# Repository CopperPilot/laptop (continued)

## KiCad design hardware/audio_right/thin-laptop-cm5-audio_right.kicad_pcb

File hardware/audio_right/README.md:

# Right Audio & Microphone Sub-Board (`audio_right`)

## Overview
- **Project**: `hardware/audio_right/thin-laptop-cm5-audio_right.kicad_pro`
- **Dimensions**: `36.0 mm x 38.0 mm`, 2-layer FR-4 PCB (`1.6 mm` thickness, `2.0 mm` corner radius)
- **World Placement**: `[190.5, -4.0, 0.0] mm` inside the 13-inch thin aluminum laptop lower deck
- **Mating Cable (`c_audio_right`)**: 8-pin `0.5 mm` pitch **Type-B (opposite-side / reversed-contact)** FFC ribbon (`45.0 mm` length) connecting main-board bottom-contact `J_AUDR` (`FPC-05F-8PH20`, LCSC `C2856797`, contacts `-Z`, Pad 1 at South `y=23.75 mm`, Pad 8 at North `y=20.25 mm`) 1-to-1 to `audio_right` top-contact `J2` (`FPC-05FB-8PH20`, LCSC `C2856828`, contacts `+Z`, Pad 1 at South `y=19.75 mm`, Pad 8 at North `y=16.25 mm`)

---

## Sub-Board Architecture & Design Review Verification

1. **CTIA / AHJ 3.5 mm 6-Pin Switched TRRS Jack Mapping (`J1`, XKB Connection `PJ-3701-SMT`, LCSC `C2684645`, `[P1]` Resolved)**:
   - Replaced unswitched 4-pin `PJ-320D` with 6-pin `XKB Connection PJ-3701-SMT` (LCSC `C2684645`, `lcsc:AUDIO-SMD_PJ-3701-SMT`) placed at `(28.50, 19.00) mm`, `rot = 180.0 deg` on `F.Cu` (`mouth` facing `+X` `[1, 0, 0]` into right-edge case cutout `F_AUDIO`).
   - Verified pin-to-contact mapping against the `PJ-3701-SMT` mechanical drawing and schematic (`SCHEMATIC(PLUG OUT)`):
     - **Pin 4 (Tip, `12.21 mm` deepest contact at pad `(24.02, 22.85) mm`)**: `/HP_L_JACK` (Left headphone audio).
     - **Pin 3 (Ring 1, `4.79 mm` middle contact at pad `(30.02, 22.85) mm`)**: `/HP_R_JACK` (Right headphone audio).
     - **Pin 2 (Ring 2, `7.84 mm` common return contact at pad `(32.98, 15.15) mm`)**: `/GND` (CTIA common ground return, Kelvin-sensed via `C20 = 2.2 uF` placed at `(32.30, 12.50) mm` with dedicated `F.Cu` Kelvin trace directly to `J1.2` and `R29 = 1.3 kOhm` into `/HS_REF_MUX`).
     - **Pin 1 (Sleeve, `1.81 mm` entrance contact at pad `(31.92, 22.85) mm`)**: `/HS_MIC_DET` (CTIA headset microphone & bias/sense, clamped by unidirectional 3.3 V ESD diode `D3` `PESD3V3U1UA,115`, LCSC `C403915`).
     - **Pin 5 (`/TIP_SW` at pad `(24.02, 15.15) mm`) & Pin 6 (`/GND` at pad `(26.02, 15.15) mm`)**: Isolated Normally-Closed (NC) Mechanical Tip Plug-Detect Switch (`5 VDC`, `0.5 A`, `<= 70 mOhm` closed resistance). When unplugged (`PLUG OUT`), Pin 5 is shorted to Pin 6 (`/GND`), holding `/TIP_SW = 0.000 V`. When any 3.5 mm plug is fully seated, Tip lifts insulator block `#9` to open Pin 5 from Pin 6, allowing `/TIP_SW` to charge via `R30 = 22 kOhm` (`C25768`) toward `/+2V8_ANA` (`2.80 V`) across `C23 = 2.2 uF` (`C159814`, `tau = 48.4 ms`, crossing `U1` rising threshold `V_TH+ = 2.365 V` at `t_qual = 90.1 ms` after contact bounce and Sleeve insertion wiping have completed), protected by ESD diode `D10` (`PESD3V3U1UA,115`, LCSC `C403915`).

2. **Decoupled Mechanical Headphone Plug Detection (`U1`) & Deterministic Monostable Microphone Source Selection (`U2, U3`, `3x TI TLV7041DBVR`, LCSC `C702122`, `[P1]` & `[P2]` Resolved)**:
   - **Headphone Plug Detection (`U1` driving `/HP_DET_N -> R4 = 1 kOhm -> /HP_DET` on `J2.7`)**:
     - `U1.4` (`IN-`) senses `/TIP_SW`; `U1.3` (`IN+`) senses `/U1_INP` (`V_REF_HI = 2.344 V` via `R23 = 22 kOhm` with `R31 = 1 MOhm` positive feedback to `/HP_DET_N`, giving `V_TH+ = 2.365 V` rising at `t = 90.1 ms` and `V_TH- = 2.293 V` falling, `72 mV` hysteresis).
     - `/HP_DET` is **100% independent of Sleeve microphone impedance**: inline hardware mic-mute switches (`R_sleeve = inf`), detached boom mics, or open-mic Y-splitters never cause false unplug events on `/HP_DET`.
   - **Synchronous Debounced Plug-Presence Gate (`U2`) & Deterministic 3-Pole TRS vs 4-Pole CTIA Classifier (`U3`) on `/MIC_SEL` (`R17 = 2.2 kOhm` pull-up to `/+3V3`)**:
     - Reference divider on `/+2V8_ANA` (`2.80 V`): `R13 = 2.2 kOhm`, `R14 = 10 kOhm`, `R16 = 1.3 kOhm` (`C25866`) -> `V_REF_HI = 2.344 V` (`C17 = 100 nF`), `V_REF_LO = 0.270 V` (`C18 = 100 nF`).
     - **Synchronous Plug-Presence Gate (`U2`)**: `U2.3` (`IN+`) = `/V_REF_HI` (`2.344 V`), `U2.4` (`IN-`) = `/HP_DET_N` (driven directly by `U1.1`'s debounced output with `72 mV` hysteresis). Whenever unplugged (`V_TIP_SW < 2.365 V`) or during the first `90.1 ms` of plug insertion (`/HP_DET_N = 3.30 V`), `U2.1` holds `/MIC_SEL` LOW (`0.00 V`, selecting internal MEMS mic `MK1`). Once `U1` qualifies the seated plug at `t = 90.1 ms` (`/HP_DET_N = 0.00 V`), `U2.1` releases `/MIC_SEL` synchronously with `/HP_DET_N`.
     - **Non-Loading Sleeve Sense Tap & Rail-to-Rail Clamp (`R12, C12, D11`)**:
       - Sleeve `/HS_MIC_DET` is sensed through high-impedance `R12 = 47 kOhm` (`C25792`) and `C12 = 4.7 nF` (`C1538`, `tau = 221 us << 90.1 ms`), loading the positive mic leg by `< 0.2 dB` across `20 Hz .. 20 kHz` so `/HS_MIC_MUX` (`1.29 kOhm .. 1.32 kOhm`) stays balanced within `1.5%` of `/HS_REF_MUX` (`R29 = 1.30 kOhm`).
       - `D11` (`BAV99,215`, LCSC `C2500`, `I_R < 1 nA` typ) clamps `/DET_IN` between `/GND` (Pin 1) and `/+2V8_ANA` (Pin 2) behind `R12 = 47 kOhm`, ensuring `/DET_IN` never exceeds `-0.3 V` or `+2V8_ANA + 0.3 V`.
     - **Deterministic 3-Pole TRS vs 4-Pole CTIA Selection (`U3`)**:
       - `U3.4` (`IN-`) = `/V_REF_LO` (`0.270 V`); `U3.3` (`IN+` = `/U3_INP`) is connected via `R27 = 2.2 kOhm` (`C25879`) to `/DET_IN` with `R28 = 1 MOhm` (`C26083`) hysteresis to `/MIC_SEL`.
       - **3-Pole TRS Headphones (`R_sleeve < 100 Ohm`, e.g. `0 Ohm` grounded Sleeve)**: `V_HS_MIC_DET < 0.100 V` settles on `/DET_IN` in `< 1.1 ms << 90.1 ms`. Even if `/MIC_SEL` were transiently `3.30 V`, `V_U3P(R_sleeve = 0 Ohm, MIC_SEL = 3.30 V) = 3.30 V * (47k + 2.2k) / (47k + 2.2k + 1000k) = 0.155 V < V_REF_LO (0.270 V)` (`V_TH- = 0.121 V` [`120 Ohm`], `V_TH+ = 0.283 V` [`300 Ohm`]). Thus `U3.1` deterministically holds or resets `/MIC_SEL = 0.00 V` (internal mic `MK1`) with **zero bistable lockup** on TRS contact bounce.
       - **4-Pole CTIA Headset (`680 Ohm <= R_sleeve <= 10 kOhm`, or `R_sleeve = inf` when inline hardware mute switch is open at boot, plug-in, or during capture)**: `0.568 V <= V_HS_MIC_DET <= 2.800 V -> 0.541 V <= V_U3P <= 2.823 V > V_REF_LO (0.270 V)`. Both `U2.1` and `U3.1` release `/MIC_SEL` to `3.30 V`, switching `U4` (`TS5A23159DGSR`) to the external headset microphone (`NO1/NO2`) so a muted CTIA headset never silently falls back to internal mic `MK1`.

3. **Ultra-Low-Noise 2.8 V Analog LDO & Back-Drive Protection (`U5`, TI `LP5907MFX-2.8/NOPB`, LCSC `C186700`, `R24`, `D12`, `[P1]` Resolved)**:
   - Powered from `/+3V3` with local `1 uF` input cap `C22` (`C52923`) within `1.5 mm` of `U5.1`/`U5.2` and local `1 uF` output cap `C21` (`C52923`) on `/+2V8_ANA`.
   - `R24 = 1.3 kOhm` (`C25866`) minimum preload bleeder from `/+2V8_ANA` to `/GND` (`2.154 mA`) combines with the reference dividers (`0.237 mA`) and `MK1` (`0.185 mA` min) to guarantee `>= 2.575 mA` continuous sink load on `/+2V8_ANA`, exceeding the maximum back-drive current (`(6.0 V - 2.8 V) / (2.67k || 47k) = 1.27 mA`) under external `3 V .. 6 V` faults on `J1.1` before `D3` (`PESD3V3U1UA,115`) and `D12` (`PESD3V3U1UA,115` on `/+2V8_ANA`) clamp to `/GND`.

4. **Dual SPDT Differential Microphone Multiplexer (`U4`, TI `TS5A23159DGSR`, LCSC `C42751`) & Matched Low-Leakage Silicon Clamps (`D8, D9`, `BAV99,215`, LCSC `C2500`)**:
   - Biased at `/MUX_BIAS_FILT = 0.795 V` via `R18 = 68 kOhm` (`C36871`) and `R19 = 27 kOhm` (`C25771`) from `/+2V8_ANA`, matching `MK1` (`ICS-40720`) `0.80 V` DC common-mode output within `5 mV` for clickless switching.
   - Clamped by matched ultra-low-leakage dual-series silicon diodes `D8` (on `/HS_MIC_MUX`) and `D9` (on `/HS_REF_MUX`) between `/GND` and `/+3V3`.

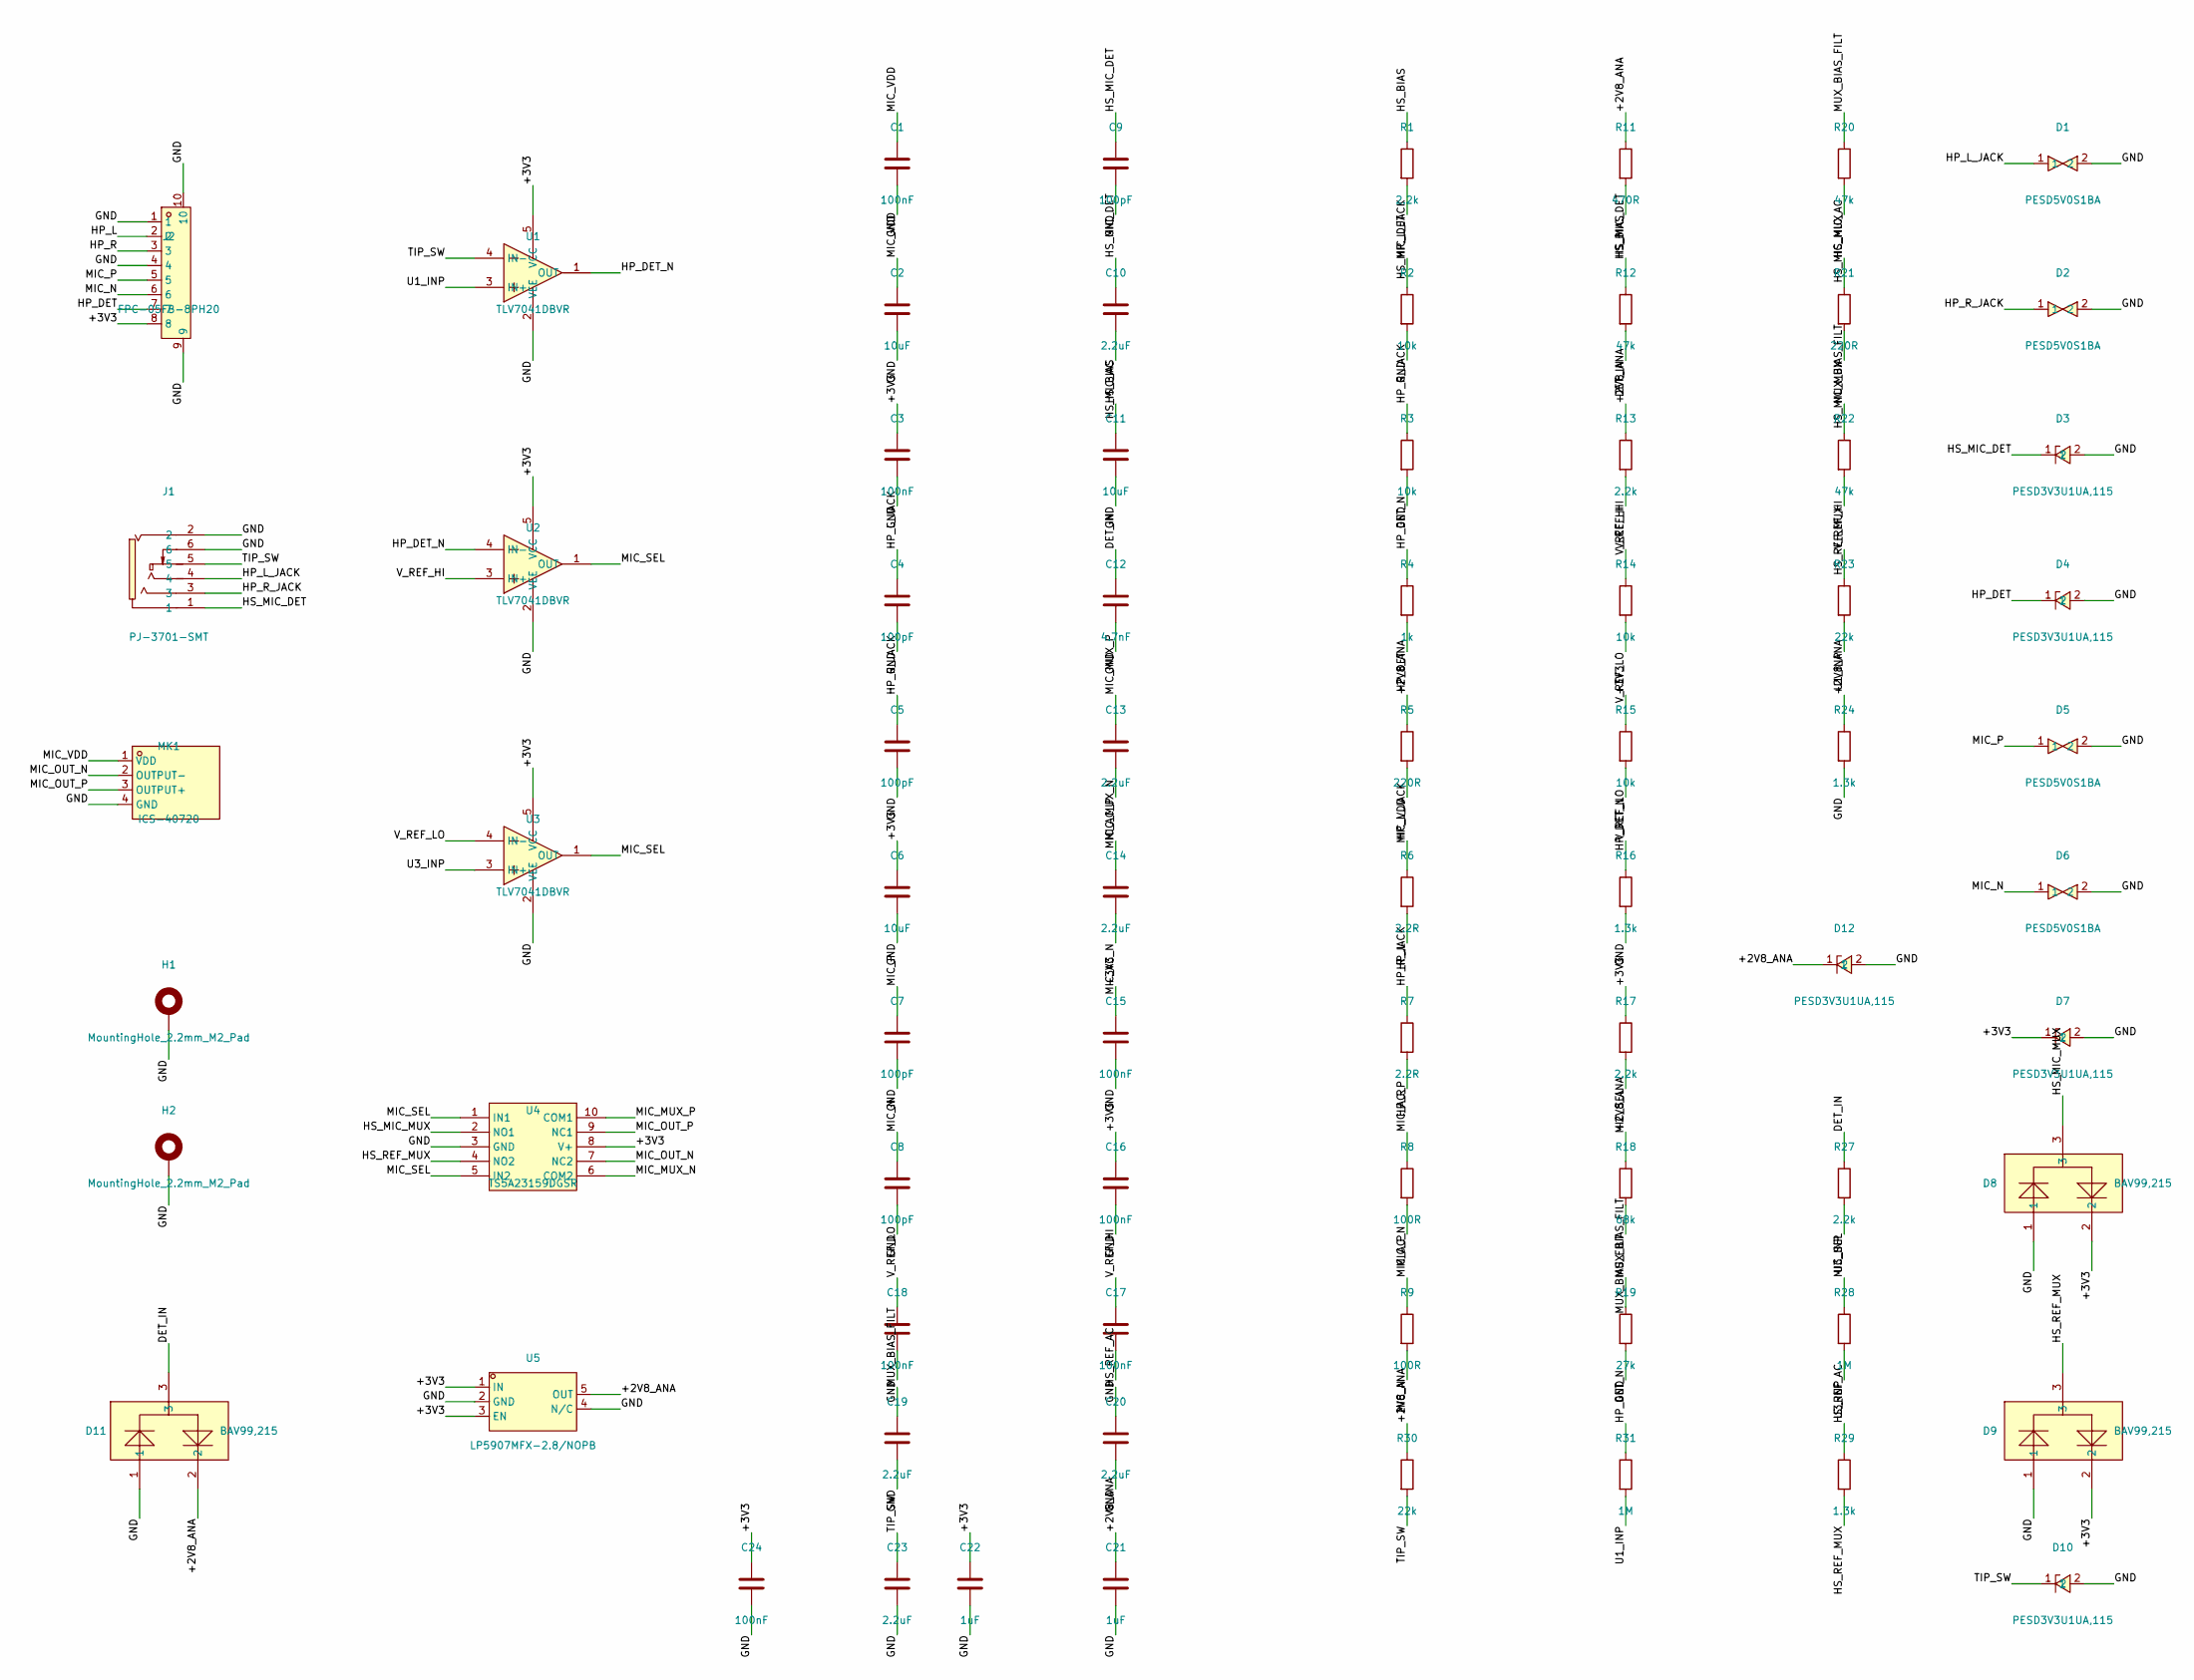
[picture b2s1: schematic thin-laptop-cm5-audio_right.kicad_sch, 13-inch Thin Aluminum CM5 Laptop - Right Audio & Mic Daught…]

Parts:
C1, C3, C15, C16, C17, C18, C24: 100nF; C_0402_1005Metric; LCSC C85858
C2, C6, C11: 10uF; C_0603_1608Metric; LCSC C96446
C4, C5, C7, C8, C9: 100pF; C_0402_1005Metric; LCSC C1546
C10, C13, C14, C19, C20, C23: 2.2uF; C_0402_1005Metric; LCSC C159814
C12: 4.7nF; C_0402_1005Metric; LCSC C1538
C21, C22: 1uF; C_0402_1005Metric; LCSC C52923
D1, D2, D5, D6: PESD5V0S1BA; SOD-323_L1.7-W1.3-LS2.5-BI; LCSC C2827694
D3, D4, D7, D10, D12: PESD3V3U1UA,115; SOD-323_L1.7-W1.3-LS2.5-RD; LCSC C403915
D8, D9, D11: BAV99,215; SOT-23-3_L2.9-W1.6-P1.90-LS2.8-BR; LCSC C2500
H1, H2: MountingHole_2.2mm_M2_Pad
J1: PJ-3701-SMT; AUDIO-SMD_PJ-3701-SMT; LCSC C2684645
J2: FPC-05FB-8PH20; FPC-SMD_8P-P0.50_XUNPU_FPC-05FB-8PH20; LCSC C2856828
MK1: ICS-40720; SMD_4P-P0.88_ICS-40720; LCSC C3171779
R1, R13, R17, R27: 2.2k; R_0402_1005Metric; LCSC C25879
R2, R3, R14, R15: 10k; R_0402_1005Metric; LCSC C25744
R4: 1k; R_0402_1005Metric; LCSC C11702
R5, R21: 220R; R_0402_1005Metric; LCSC C25091
R6, R7: 2.2R; R_0402_1005Metric; LCSC C25101
R8, R9: 100R; R_0402_1005Metric; LCSC C25076
R11: 470R; R_0402_1005Metric; LCSC C25117
R12, R20, R22: 47k; R_0402_1005Metric; LCSC C25792
R16, R24, R29: 1.3k; R_0402_1005Metric; LCSC C25866
R18: 68k; R_0402_1005Metric; LCSC C36871
R19: 27k; R_0402_1005Metric; LCSC C25771
R23, R30: 22k; R_0402_1005Metric; LCSC C25768
R28, R31: 1M; R_0402_1005Metric; LCSC C26083
U1, U2, U3: TLV7041DBVR; SOT-23-5_L2.9-W1.6-P0.95-LS2.8-BR; LCSC C702122
U4: TS5A23159DGSR; VSSOP-10_L3.0-W3.0-P0.50-LS4.9-BL; LCSC C42751
U5: LP5907MFX-2.8/NOPB; TSOT-23-5_L2.9-W1.6-P0.95-LS2.8-BL; LCSC C186700

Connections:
/+2V8_ANA: C21.1, D11.2, D12.1, R5.1, R11.1, R13.1, R18.1, R24.1, R30.1, U5.5 (OUT)
/+3V3: C3.1, C6.1, C15.1, C16.1, C22.1, C24.1, D7.1, D8.2, D9.2, J2.8, R15.1, R17.1, U1.5 (VCC), U2.5 (VCC), U3.5 (VCC), U4.8 (V+), U5.1 (IN), U5.3 (EN)
/DET_IN: C12.1, D11.3, R12.2, R27.1
/GND: C1.2, C2.2, C3.2, C4.2, C5.2, C6.2, C7.2, C8.2, C9.2, C11.2, C12.2, C15.2, C16.2, C17.2, C18.2, C19.2, C20.2, C21.2, C22.2, C23.2, C24.2, D1.2, D2.2, D3.2, D4.2, D5.2, D6.2, D7.2, D8.1, D9.1, D10.2, D11.1, D12.2, H1.1, H2.1, J1.2, J1.6, J2.1, J2.4, J2.9, J2.10, MK1.4 (GND), R2.2, R3.2, R16.2, R19.2, R24.2, U1.2 (VEE), U2.2 (VEE), U3.2 (VEE), U4.3 (GND), U5.2 (GND), U5.4 (N/C)
/HP_DET: D4.1, J2.7, R4.2
/HP_DET_N: R4.1, R15.2, R31.1, U1.1 (OUT), U2.4 (IN-)
/HP_L: J2.2, R6.2
/HP_L_JACK: C4.1, D1.1, J1.4, R2.1, R6.1
/HP_R: J2.3, R7.2
/HP_R_JACK: C5.1, D2.1, J1.3, R3.1, R7.1
/HS_BIAS: C11.1, R1.1, R11.2
/HS_MIC_AC: C10.2, R21.1
/HS_MIC_DET: C9.1, C10.1, D3.1, J1.1, R1.2, R12.1
/HS_MIC_MUX: D8.3, R20.2, R21.2, U4.2 (NO1)
/HS_REF_AC: C20.1, R29.1
/HS_REF_MUX: D9.3, R22.2, R29.2, U4.4 (NO2)
/MIC_AC_N: C14.2, R9.1
/MIC_AC_P: C13.2, R8.1
/MIC_MUX_N: C14.1, U4.6 (COM2)
/MIC_MUX_P: C13.1, U4.10 (COM1)
/MIC_N: C8.1, D6.1, J2.6, R9.2
/MIC_OUT_N: MK1.2 (OUTPUT−), U4.7 (NC2)
/MIC_OUT_P: MK1.3 (OUTPUT+), U4.9 (NC1)
/MIC_P: C7.1, D5.1, J2.5, R8.2
/MIC_SEL: R17.2, R28.1, U2.1 (OUT), U3.1 (OUT), U4.1 (IN1), U4.5 (IN2)
/MIC_VDD: C1.1, C2.1, MK1.1 (VDD), R5.2
/MUX_BIAS_FILT: C19.1, R18.2, R19.1, R20.1, R22.1
/TIP_SW: C23.1, D10.1, J1.5, R30.2, U1.4 (IN-)
/U1_INP: R23.2, R31.2, U1.3 (IN+)
/U3_INP: R27.2, R28.2, U3.3 (IN+)
/V_REF_HI: C17.1, R13.2, R14.1, R23.1, U2.3 (IN+)
/V_REF_LO: C18.1, R14.2, R16.1, U3.4 (IN-)

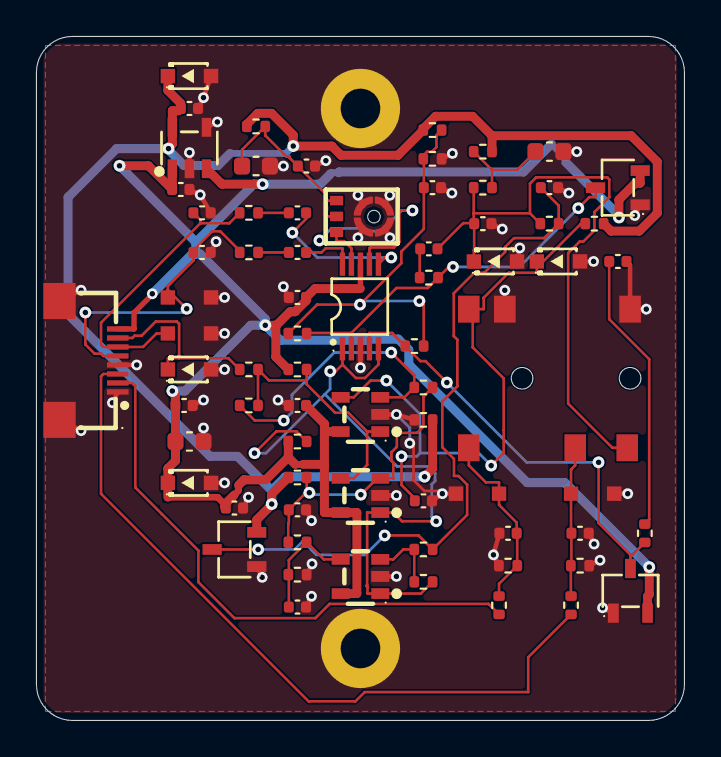
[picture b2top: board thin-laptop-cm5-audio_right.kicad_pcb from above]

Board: 2 copper layers, 36.0 x 38.0 mm, 74 parts (0 on the bottom side), 32 nets.

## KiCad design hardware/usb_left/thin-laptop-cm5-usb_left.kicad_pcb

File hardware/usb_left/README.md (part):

# Left Dual USB-C PD & Data Daughter Board (`usb_left`)

## 1. Architecture & Block Summary (`usb_left_subboard`)

`usb_left` is a **4-layer 1.6 mm controlled-impedance FR-4 PCB** (matching the main board stackup with `0.1068 mm` outer prepreg over continuous `In1.Cu`, `In2.Cu`, and `B.Cu` `GND` reference planes). All components on `usb_left` are assembled on the top side (`F.Cu` only, `0` bottom-side components) so the CNC aluminum `bottom_shell` underneath `usb_left` is a continuous unperforated pan with no through-cutouts.

### 1.1 Front-Left 20 V (45 W Hardware-Capped from 45–65 W Adapters, with 5 V–20 V Autonomous Dead-Battery VINDPM Startup) USB-C PD 3.0 Charging & Host Data Port (`J2`, `TYPE-C-31-M-12`, LCSC `C165948`)
- **Autonomous Hardware USB-PD 3.0 Sink Controller (`U1`, `CH224A`, LCSC `C42459160`):**
  - `U1` (`CH224A` in ESSOP-10, 4 V–30 V operating range) negotiates **20 V USB-PD 3.0 contracts** from 45 W–65 W (`20 V @ 2.25 A–3.25 A`) USB-C PD adapters autonomously in hardware with no processor or I2C controller required (automatically falling back to the highest offered PDO `15 V -> 12 V -> 9 V -> 5 V` per `CH224` Datasheet Section 5.2 when `<20 V` adapters are connected), feeding the main-board `BQ25798RQMR` 5 A 2S buck-boost NVDC battery charger (`3.6 V–24 V` operating input, `26 V` `VBUS_OVP`, with hardware `VINDPM` [`4.3 V` floor at `5 V`, `V_VBUS0 - 1.4 V` at `12 V–20 V`] and hardware `ILIM_HIZ = 2.25 A` / `45 W` input limit set by `R29 = 78.7 kOhm` / `R30 = 100 kOhm`) over the 1.0 mm 5 A-rated harness `J5`.
  - Configured for **20 V PD request** using single-resistor `CFG1` strapping per WCH `CH224` Datasheet Section 5.2.1:
    - Pin 9 (`CFG1`, net `/PD_CFG1`) is strapped to `GND` via `R11 = 120 kOhm` 1% 0402 (`0402WGF1203TCE`, LCSC `C25750`) to request `20 V`.
    - Pins 2 (`CFG2_SCL`) and 3 (`CFG3_SDA`) are left open (`NC`, biased solely by `U1`'s internal pull-ups to its own internal `VDD33` rail), completely eliminating any external rail connection to `CFG2` and preventing CMOS back-powering when `U1.1` (`VHV`) is at `0 V`.
  - Pin 1 (`VHV`, internal 4.0 V–30 V LDO input) and Pin 8 (`VBUS`, voltage sense input) are tied directly together on net `/PD_VHV`, which connects directly to unswitched receptacle rail `/J2_VBUS` via 0-ohm jumper `R3 = 0R` 0603 (`0603WAF0000T5E`, LCSC `C21189`) and is decoupled to `GND` by `C5 = 1 uF` 50 V X5R 0603 (`CL10A105KB8NNNC`, LCSC `C15849`) per the `CH224A` application circuit (eliminating series voltage drop on `VHV` during 5 V cold-socket attach).
  - Pins 4 and 5 (`DP`, `DM`) are left unconnected (`NC`) per `CH224` Datasheet Section 5.5 (`Use PD protocol only`) so `J2` USB 2.0 host data lines pass undisturbed to the CM5 RP1 controller.
  - Pin 10 (`PG`, open-drain active-low 20 V Power Good indicator on `/PD_PG_N`) is pulled up to `/PD_VDD_3V3` (`3.3 V`) via `R5 = 10 kOhm` (`0402WGF1002TCE`, LCSC `C25744`) and drives a non-inverting 2-stage `2N7002` open-drain cross-domain buffer (`Q3` + `Q6`, LCSC `C8545`: `Q3` Gate on `/PD_PG_N`, Source on `/GND`, Drain `/PD_PG_INV` pulled up to `/PD_VDD_3V3` via `R24 = 100 kOhm` `C25741` driving `Q6` Gate, `Q6` Source on `/GND`, `Q6` Drain `/PD_PG_ISO` routed via `R16 = 1 kOhm` `C11702` to `J3` pin 1 `/USBL_PD_PG_N` and pulled up exclusively to the receiving main-board `/+3V3` domain via `R75 = 10 kOhm`, with `R25` removed), delivering CMOS-compliant active-low `20 V PD Power Good` telemetry (`V_OL = 0.065 V << 0.80 V = V_IL(max)` when `20 V` PD contract is active, `V_OH = 3.30 V > 2.00 V = V_IH(min)` when `<20 V` fallback source is attached or `J2` is unattached, with `0.0 uA` cross-domain bleed into `/J1_VDD_3V3` or `/+5V_USBC` in all power states).
- **Cold-Socket `cSnkPwr` Compliance (`<= 4.7 uF`), 22 V Flat-Clamping Surge TVS (`D6`, `D7` `ESTVS2200DRVR`), & `/U3_FLT_N`-Enabled Common-Source Back-to-Back PFET Load Switch (`Q1`, `Q2` `AO4407A` + `Q4` `2N7002`):**
  - Unswitched capacitance on `/J2_VBUS` (`J2.A4B9`, `J2.B4A9`) is strictly limited to `C12 = 1 uF` 50 V 0603 (`C15849`) + `C13 = 100 nF` 50 V 0402 (`C307331`) = **`1.1 uF` (`<= 4.7 uF` and `<= 10 uF` USB Type-C `cSnkPwr` max)**, with precision flat-clamping 22 V surge TVS `D6` (`ESTVS2200DRVR`, LCSC `C42400188`, `V_RWM = 22 V`, `V_BR = 25.8 V`, `V_C = 28.6 V max < 30 V` at 70 A 8/20 us) and bleed resistor `R2 = 10 kOhm` 0603 (`C25804`).
  - Downstream bulk capacitance on `/VBUS_PD` (`C15 = 10 uF` 50 V X5R 0805 `GRM21BR61H106KE43L`, LCSC `C440198` + `C16 = 100 nF` 50 V 0402 `C307331` + `D7 = ESTVS2200DRVR` `C42400188` at `J5`, plus main-board charger input capacitors) is isolated behind adjacent back-to-back **common-source** P-MOSFETs `Q1` (`(4.85, 35.30, rot=90)`) and `Q2` (`(12.80, 35.30, rot=-90)`) (`2x AO4407A`, LCSC `C2841482`, `-30 V`, `-12 A`, `13 mOhm` SOP-8):
    - `Q1` Drain (pins 5..8) connects to the `/J2_VBUS` `F.Cu` polygon pour; `Q1` and `Q2` common Source (pins 1..3) face each other directly across a continuous `F.Cu` polygon pour and copper bars on `/PD_SW_MID`; and `Q2` Drain (pins 5..8) connects to the `/VBUS_PD` `F.Cu` polygon pour feeding `J5`.
    - **Autonomous 5 V–20 V Dead-Battery Startup & CC OVP Fault Shutdown (`Q4` `2N7002` + `R15 = 47 kOhm` from `/U3_FLT_N`):**
      - Provided `U3` (`TPD6S300RUKR`) detects no CC OVP fault (`U3.9 ~FLT` high-Z, pulled up to `/PD_VDD_3V3 = 3.30 V` via `R6 = 10 kOhm` and driving only the insulated gate of `Q5` `2N7002` so `V(/U3_FLT_N) = 3.30 V >> 2.50 V = V_GS(th,max)` of `Q4` with `0.0 uA` main-board loading), `R15 = 47 kOhm` 1% 0402 (`0402WGF4702TCE`, LCSC `C25792`) pulls `/PD_EN` (`Q4.1` Gate) to `3.30 V`, turning `Q4` (`2N7002`, LCSC `C8545`) and `Q1/Q2` ON autonomously across the full `5 V–20 V` USB-C input range.
      - During dead-battery startup on `<20 V` (`5 V, 9 V, 12 V, 15 V`) or `20 V` USB-C adapters, `/VBUS_PD` (`J5`) powers main-board buck-boost charger `U_CHG` (`BQ25798RQMR`, `3.6 V–24 V` operating input), whose hardware **Input Voltage Dynamic Power Management (`VINDPM`)** automatically measures unloaded `V_VBUS0` prior to converter start (`VINDPM = 4.3 V` at `5 V`, `8.3 V` at `9 V`, `V_VBUS0 - 1.4 V` at `12 V–20 V`, per TI `BQ25798` Datasheet Section 8.3.3.2) and throttles input current in hardware whenever a `<20 V` source droops toward `VINDPM`, preventing adapter collapse without requiring host software while `ILIM_HIZ = 2.25 A` caps `20 V` PD input power at `45 W`.
      - When the CM5 is running, `U_CHG` immediately detects VBUS attachment on `/VBUS_PD` (asserting `/CHG_INT_N` to `CM5 GPIO5` and measuring exact input voltage via its 16-bit `VBUS_ADC` over I2C) while `J3.1` (`/USBL_PD_PG_N`) reports hardware `20 V PD Power Good` status (`LOW = 20 V PD contract`, `HIGH = <20 V fallback source`).
    - **Zero-Divider Full-Swing Gate Drive, Fast `~45 us` Fault Turn-Off, & Diode-Isolated Miller Pre-Charge (`R13 = 10 kOhm`, `R14 = 10 kOhm`, `D9`, `C17`, `D10`, `R22`, `D11`):**
      - When `Q4` is OFF (`/PD_EN = 0 V`), `R13 = 10 kOhm` 0603 (`0603WAF1002T5E`, LCSC `C25804`) pulls `Q4` Drain `/PD_DRV_D` up to the common-source midpoint `/PD_SW_MID` while dedicated series gate resistor `R14 = 10 kOhm` 0603 (`0603WAF1002T5E`, LCSC `C25804`) between `/PD_DRV_D` and `/PD_SW_G` and 12 V 500 mW Zener diode `D9` (`BZT52C12`, LCSC `C173429`, Cathode on `/PD_SW_MID`, Anode on `/PD_SW_G`) hold `V_GS1 = V_GS2 = 0 V` regardless of polarity, and discharge `/PD_SW_G` across `R13 + R14 = 20 kOhm` during a `U3` CC OVP fault (`|V_GS| < 1.7 V` in `~45 us`, `tau_off = 20 kOhm * 4.24 nF = 84.8 us`).
      - Miller soft-start capacitor `C17 = 10 nF` 50 V X7R 0402 (`CL05B103KB5NNNC`, LCSC `C15195`) on `/VBUS_PD` (`C17.1`) connects at `/PD_MILLER` (`C17.2`) to series blocking diode `D10` (`1N4148WS`, LCSC `C2128`, Anode on `/PD_MILLER`, Cathode on `/PD_SW_G`) and diode-isolated pre-charge network `R22 = 1 kOhm` 1% 0402 (`0402WGF1001TCE`, LCSC `C11702`) + `D11` (`1N4148WS`, LCSC `C2128`, Anode on `/PD_PRECHG` from `/PD_DRV_D` via `R22 = 1 kOhm`, Cathode on `/PD_MILLER`).
      - While `Q4` is OFF during hot-plug attach, `R13` (`10 kOhm`) + `R22` (`1 kOhm`) + `D11` pre-charge `C17` to `V(/PD_SW_MID)` with fast time constant `tau = (10k + 1k) * 10nF = 0.11 ms` (`3*tau = 0.33 ms < 0.50 ms`) while `D10` stays reverse-biased so `/PD_SW_G` is never pulled low prematurely.
      - The instant `Q4` turns ON (`V(/PD_DRV_D) = 0 V`), `D11` (`Anode` at `0 V`) becomes **reverse-biased**, completely disconnecting the pre-charge path from `/PD_MILLER` and `/PD_SW_G`. Consequently, **zero DC divider current** flows into `/PD_SW_G`: at `5 V` input, `V(/PD_SW_G) = 0 V` and `|V_GS1| = |V_GS2| = 5.00 V` (`100%` of the 5 V supply, well above `|V_GS(th,max)| = 3.0 V` and rated at `-4.5 V` `R_DS(on)`), while at `20 V` `D9` clamps `|V_GS1| = |V_GS2| = 12.0 V` (`P_R14 = 6.4 mW << 100 mW`, `P_D9 = 9.6 mW << 500 mW`) and `100%` of `C17`'s Miller displacement current flows through `D10` and `R14 = 10 kOhm` to control `dV(/VBUS_PD)/dt`.
- **24 V-Tolerant VBUS-to-CC Short Overvoltage & IEC 61000-4-2 ESD Port Protector (`U3`, `TPD6S300RUKR`, LCSC `C2649810`):**
  - Inserted between `J2` and `U1` (`CH224A`) / `J3`.
  - Connector-side pins `C_CC1` (pin 4) and `C_CC2` (pin 5) connect to `J2_CC1` (`J2.A5`) and `J2_CC2` (`J2.B5`), with dead-battery 5.1 kOhm `Rd` pins `RPD_G1` (pin 7) and `RPD_G2` (pin 6) tied to `J2_CC1` and `J2_CC2`.
  - `J2` USB 2.0 High-Speed differential pair (`J2.A6`/`B6` and `J2.A7`/`B7`) connects directly to `/USB3-0-D_P` and `/USB3-0-D_N` with low-capacitance (`2.5 pF` typ) IEC 61000-4-2 shunt ESD clamping on `U3.20` (`D1`) and `U3.19` (`D2`), while `U3` `C_SBU1`/`C_SBU2`/`SBU1`/`SBU2` are left unused (`NC`), matching the `U5` topology on `J1`.
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
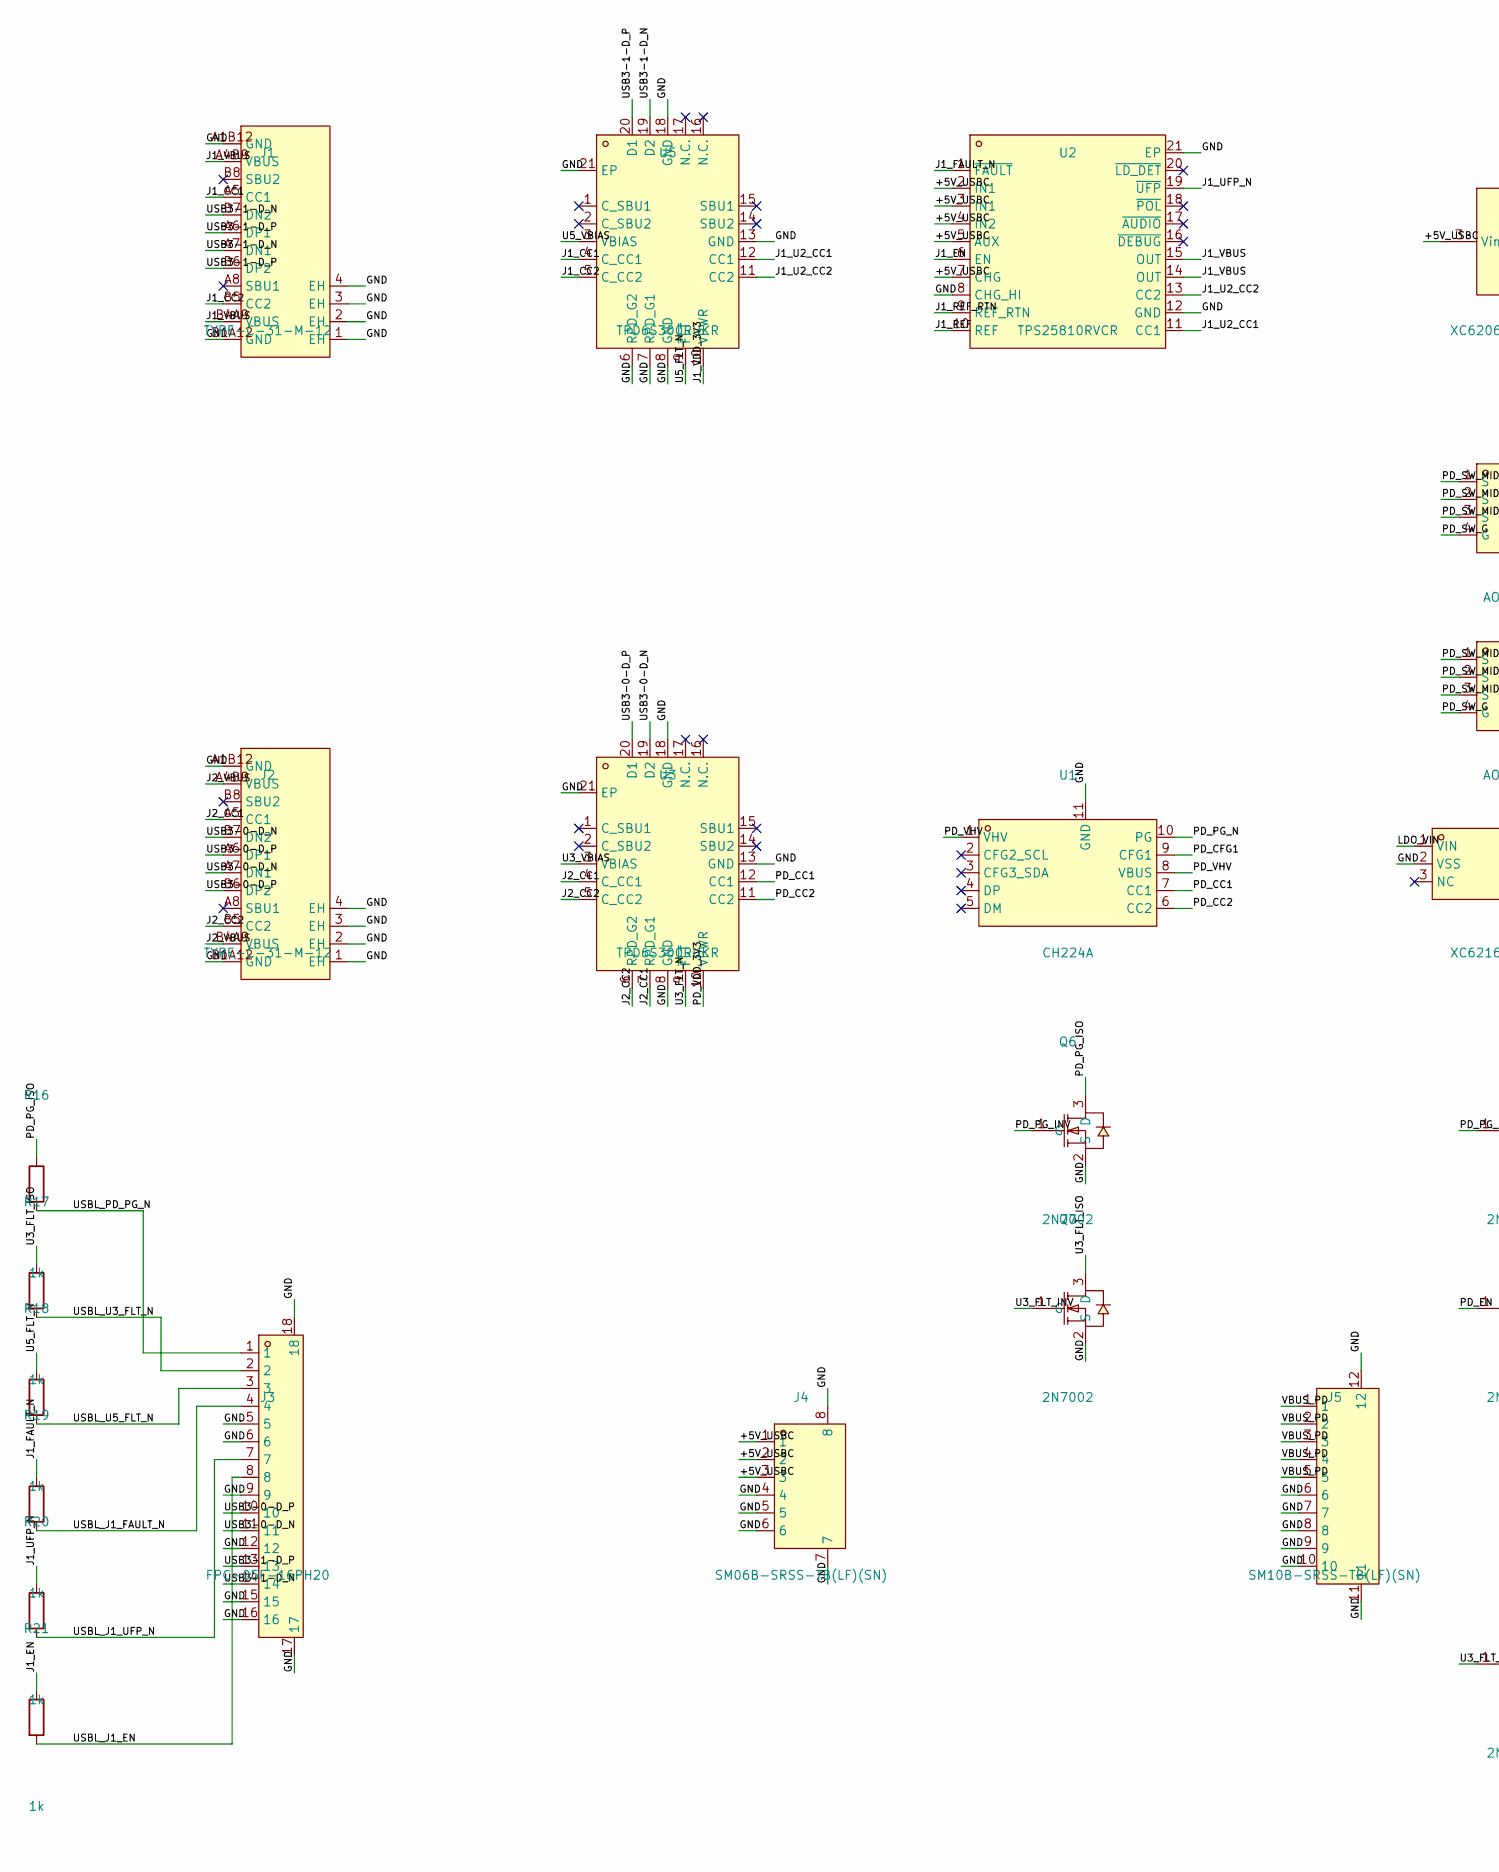
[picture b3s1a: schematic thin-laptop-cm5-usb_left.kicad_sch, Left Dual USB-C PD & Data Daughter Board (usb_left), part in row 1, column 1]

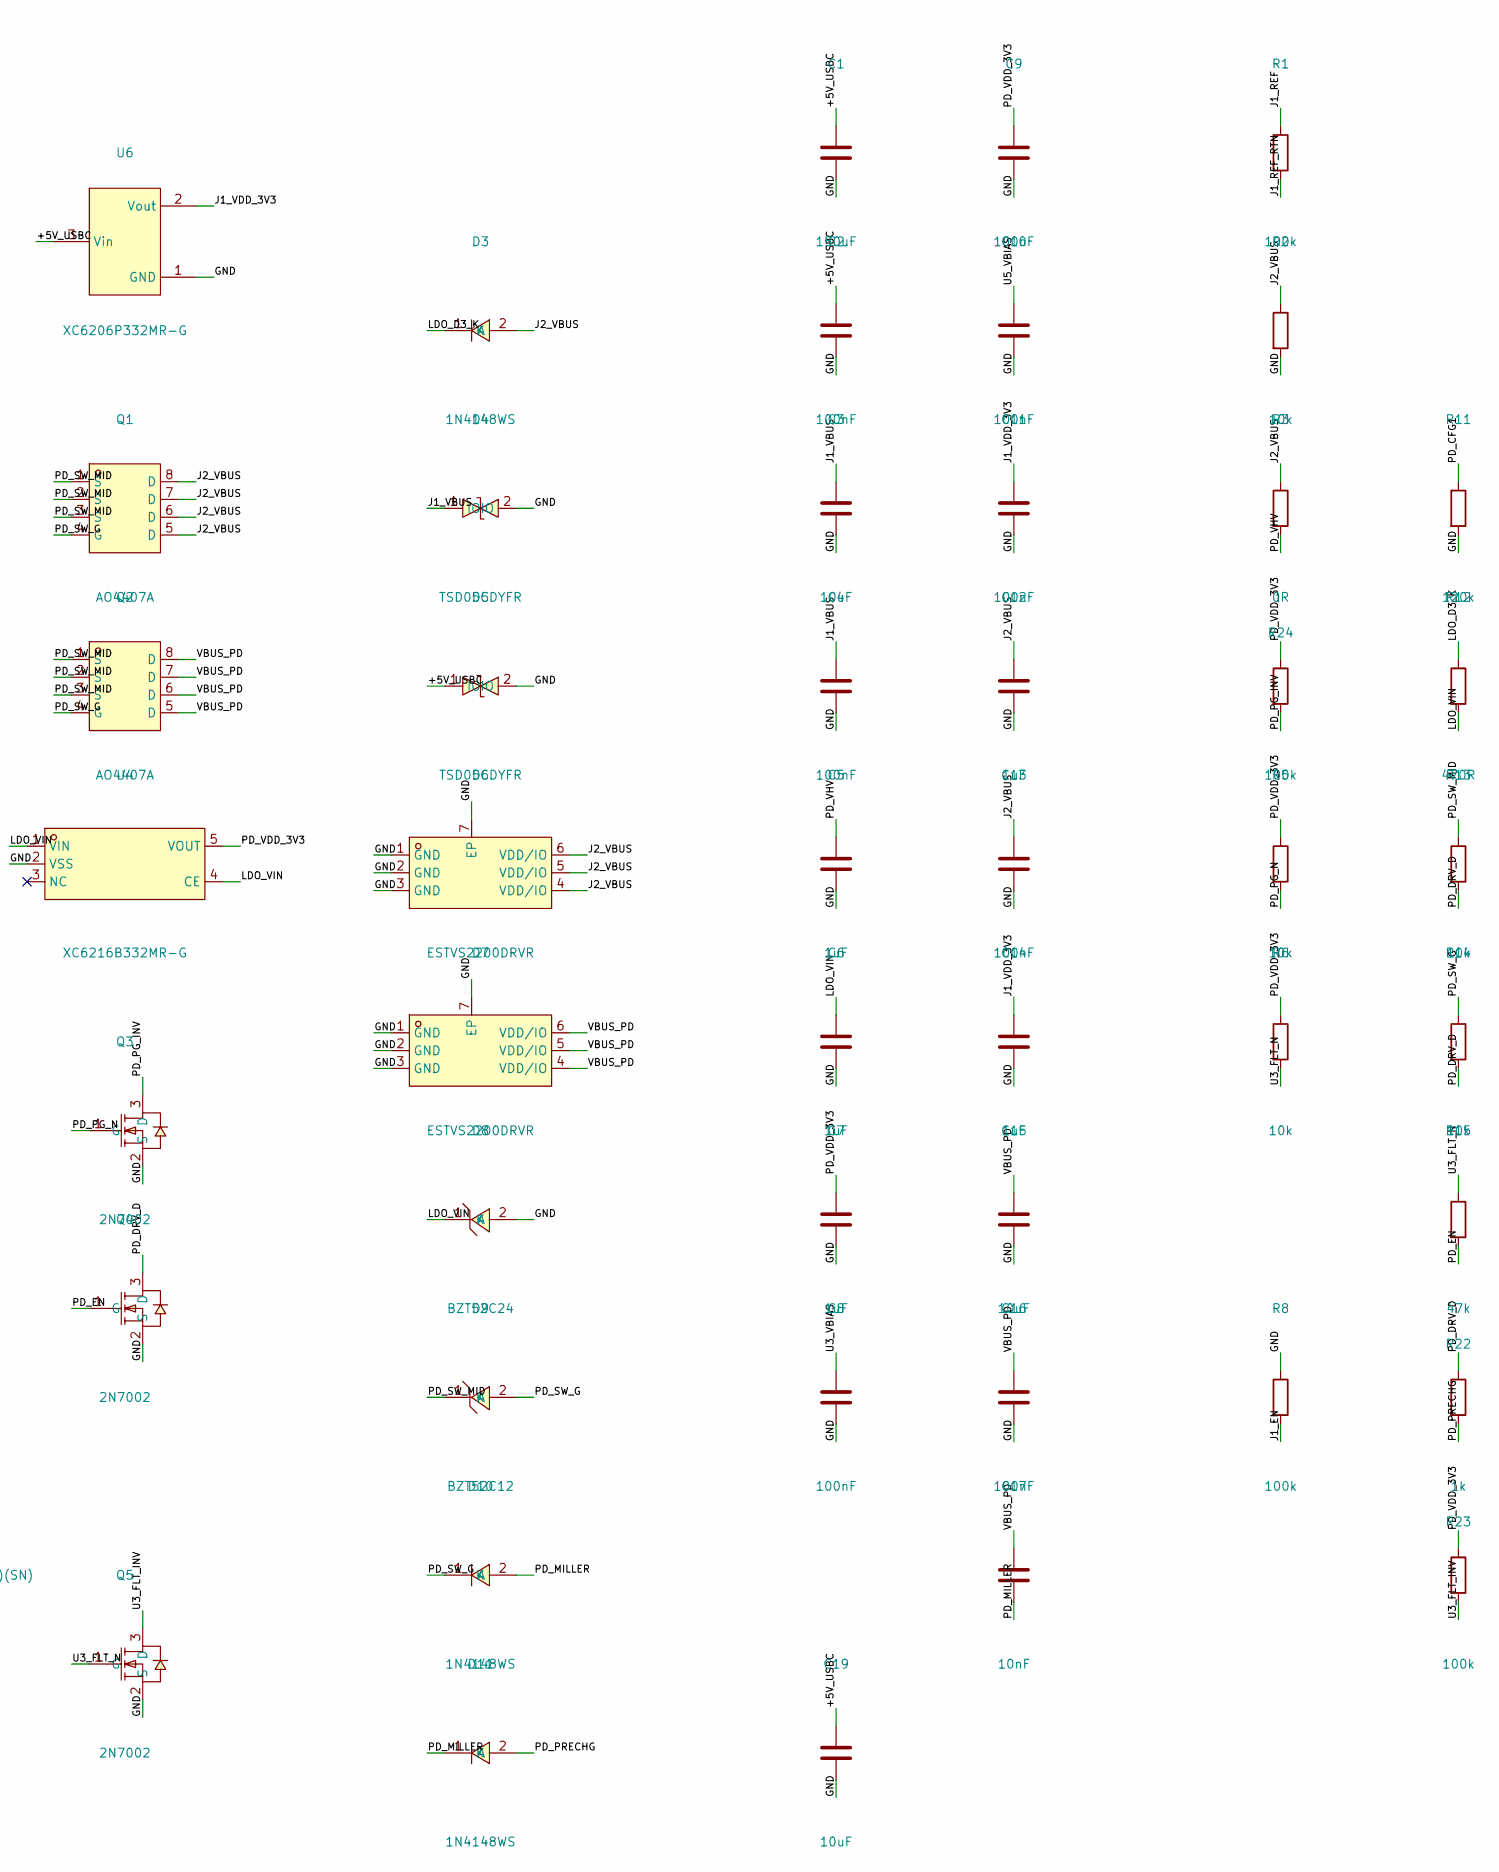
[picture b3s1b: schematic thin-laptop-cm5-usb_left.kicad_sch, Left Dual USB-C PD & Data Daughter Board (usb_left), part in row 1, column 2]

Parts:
C1: 150uF; CAP-SMD_L6.0-W3.2; MPN T520C157M010ATE055; LCSC C600588
C2, C4, C8, C9, C10, C11, C13, C16: 100nF; C_0402_1005Metric; MPN CL05B104KB54PNC; LCSC C307331
C3, C15, C19: 10uF; C_0805_2012Metric; MPN GRM21BR61H106KE43L; LCSC C440198
C5, C6, C7, C12, C14: 1uF; C_0603_1608Metric; MPN CL10A105KB8NNNC; LCSC C15849
C17: 10nF; C_0402_1005Metric; MPN CL05B103KB5NNNC; LCSC C15195
D3, D10, D11: 1N4148WS; SOD-323_L1.8-W1.3-LS2.5-RD; MPN 1N4148WS; LCSC C2128
D4, D5: TSD05CDYFR; SOD-323_L1.8-W1.3-LS2.5-BI; MPN TSD05CDYFR; LCSC C20611048
D6, D7: ESTVS2200DRVR; DFN-6_L2.0-W2.0-P0.65-BL-EP1.6; MPN ESTVS2200DRVR; LCSC C42400188
D8: BZT52C24; SOD-123_L2.7-W1.6-LS3.7-RD; MPN BZT52C24; LCSC C173422
D9: BZT52C12; SOD-123_L2.7-W1.6-LS3.7-RD; MPN BZT52C12; LCSC C173429
J1, J2: TYPE-C-31-M-12; USB-C_SMD-TYPE-C-31-M-12_1; MPN TYPE-C-31-M-12; LCSC C165948
J3: FPC-05F-16PH20; FPC-SMD_16P-P0.50_FPC-05F-16PH20; MPN FPC-05F-16PH20; LCSC C2856801
J4: SM06B-SRSS-TB(LF)(SN); CONN-SMD_SM06B-SRSS-TB-LF-SN; MPN SM06B-SRSS-TB(LF)(SN); LCSC C160405
J5: SM10B-SRSS-TB(LF)(SN); CONN-SMD_10P-P1.00_SM10B-SRSS-TB-LF-SN; MPN SM10B-SRSS-TB(LF)(SN); LCSC C160409
Q1, Q2: AO4407A; SOP-8_L5.0-W4.0-P1.27-LS6.0-BL; MPN AO4407A; LCSC C2841482
Q3, Q4, Q5, Q6, Q7: 2N7002; SOT-23-3_L2.9-W1.3-P1.90-LS2.4-BR; MPN 2N7002; LCSC C8545
R1, R8, R23, R24: 100k; R_0402_1005Metric; MPN 0402WGF1003TCE; LCSC C25741
R2, R13, R14: 10k; R_0603_1608Metric; MPN 0603WAF1002T5E; LCSC C25804
R3: 0R; R_0603_1608Metric; MPN 0603WAF0000T5E; LCSC C21189
R5, R6: 10k; R_0402_1005Metric; MPN 0402WGF1002TCE; LCSC C25744
R11: 120k; R_0402_1005Metric; MPN 0402WGF1203TCE; LCSC C25750
R12: 470R; R_0603_1608Metric; MPN 0603WAF4700T5E; LCSC C23179
R15: 47k; R_0402_1005Metric; MPN 0402WGF4702TCE; LCSC C25792
R16, R17, R18, R19, R20, R21, R22: 1k; R_0402_1005Metric; MPN 0402WGF1001TCE; LCSC C11702
U1: CH224A; ESSOP-10_L4.9-W3.9-P1.0-LS6.0-TL-EP; MPN CH224A; LCSC C42459160
U2: TPS25810RVCR; WQFN-20_L4.0-W3.0-P0.50-BL-EP; MPN TPS25810RVCR; LCSC C473913
U3, U5: TPD6S300RUKR; WQFN-20_L3.0-W3.0-P0.40-BL-EP1.7; MPN TPD6S300RUKR; LCSC C2649810
U4: XC6216B332MR-G; SOT-23-5_L3.0-W1.6-P0.95-LS2.8-BR; MPN XC6216B332MR-G; LCSC C2891269
U6: XC6206P332MR-G; SOT-23-3_L2.9-W1.6-P1.90-LS2.8-BR; MPN XC6206P332MR-G; LCSC C5446

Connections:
/+5V_USBC: C1.1, C2.1, C19.1, D5.1, J4.1, J4.2, J4.3, U2.2 (IN1), U2.3 (IN1), U2.4 (IN2), U2.5 (AUX), U2.7 (CHG), U6.3 (Vin)
/GND: C1.2, C2.2, C3.2, C4.2, C5.2, C6.2, C7.2, C8.2, C9.2, C10.2, C11.2, C12.2, C13.2, C14.2, C15.2, C16.2, C19.2, D4.2, D5.2, D6.1 (GND), D6.2 (GND), D6.3 (GND), D6.7 (EP), D7.1 (GND), D7.2 (GND), D7.3 (GND), D7.7 (EP), D8.2 (A), J1.1 (EH), J1.2 (EH), J1.3 (EH), J1.4 (EH), J1.A1B12 (GND), J1.B1A12 (GND), J2.1 (EH), J2.2 (EH), J2.3 (EH), J2.4 (EH), J2.A1B12 (GND), J2.B1A12 (GND), J3.5, J3.6, J3.9, J3.12, J3.15, J3.16, J3.17, J3.18, J4.4, J4.5, J4.6, J4.7, J4.8, J5.6, J5.7, J5.8, J5.9, J5.10, J5.11, J5.12, Q3.2 (S), Q4.2 (S), Q5.2 (S), Q6.2 (S), Q7.2 (S), R2.2, R8.1, R11.2, U1.11 (GND), U2.8 (CHG_HI), U2.12 (GND), U2.21 (EP), U3.8 (GND), U3.13 (GND), U3.18 (GND), U3.21 (EP), U4.2 (VSS), U5.6 (RPD_G2), U5.7 (RPD_G1), U5.8 (GND), U5.13 (GND), U5.18 (GND), U5.21 (EP), U6.1 (GND)
/J1_CC1: J1.A5 (CC1), U5.4 (C_CC1)
/J1_CC2: J1.B5 (CC2), U5.5 (C_CC2)
/J1_EN: R8.2, R21.1, U2.6 (EN)
/J1_FAULT_N: R19.1, U2.1 (~FAULT)
/J1_REF: R1.1, U2.10 (REF)
/J1_REF_RTN: R1.2, U2.9 (REF_RTN)
/J1_U2_CC1: U2.11 (CC1), U5.12 (CC1)
/J1_U2_CC2: U2.13 (CC2), U5.11 (CC2)
/J1_UFP_N: R20.1, U2.19 (~UFP)
/J1_VBUS: C3.1, C4.1, D4.1, J1.A4B9 (VBUS), J1.B4A9 (VBUS), U2.14 (OUT), U2.15 (OUT)
/J1_VDD_3V3: C11.1, C14.1, U5.10 (VPWR), U6.2 (Vout)
/J2_CC1: J2.A5 (CC1), U3.4 (C_CC1), U3.7 (RPD_G1)
/J2_CC2: J2.B5 (CC2), U3.5 (C_CC2), U3.6 (RPD_G2)
/J2_VBUS: C12.1, C13.1, D3.2 (A), D6.4 (VDD/IO), D6.5 (VDD/IO), D6.6 (VDD/IO), J2.A4B9 (VBUS), J2.B4A9 (VBUS), Q1.5 (D), Q1.6 (D), Q1.7 (D), Q1.8 (D), R2.1, R3.1
/LDO_D3_K: D3.1 (K), R12.1
/LDO_VIN: C6.1, D8.1 (K), R12.2, U4.1 (VIN), U4.4 (CE)
/PD_CC1: U1.7 (CC1), U3.12 (CC1)
/PD_CC2: U1.6 (CC2), U3.11 (CC2)
/PD_CFG1: R11.1, U1.9 (CFG1)
/PD_DRV_D: Q4.3 (D), R13.2, R14.2, R22.1
/PD_EN: Q4.1 (G), R15.2
/PD_MILLER: C17.2, D10.2 (A), D11.1 (K)
/PD_PG_INV: Q3.3 (D), Q6.1 (G), R24.2
/PD_PG_ISO: Q6.3 (D), R16.1
/PD_PG_N: Q3.1 (G), R5.2, U1.10 (PG)
/PD_PRECHG: D11.2 (A), R22.2
/PD_SW_G: D9.2 (A), D10.1 (K), Q1.4 (G), Q2.4 (G), R14.1
/PD_SW_MID: D9.1 (K), Q1.1 (S), Q1.2 (S), Q1.3 (S), Q2.1 (S), Q2.2 (S), Q2.3 (S), R13.1
/PD_VDD_3V3: C7.1, C9.1, R5.1, R6.1, R23.1, R24.1, U3.10 (VPWR), U4.5 (VOUT)
/PD_VHV: C5.1, R3.2, U1.1 (VHV), U1.8 (VBUS)
/U3_FLT_INV: Q5.3 (D), Q7.1 (G), R23.2
/U3_FLT_ISO: Q7.3 (D), R17.1
/U3_FLT_N: Q5.1 (G), R6.2, R15.1, U3.9 (~FLT)
/U3_VBIAS: C8.1, U3.3 (VBIAS)
/U5_FLT_N: R18.1, U5.9 (~FLT)
/U5_VBIAS: C10.1, U5.3 (VBIAS)
/USB3-0-D_N: J2.A7 (DN1), J2.B7 (DN2), J3.11, U3.19 (D2)
/USB3-0-D_P: J2.A6 (DP1), J2.B6 (DP2), J3.10, U3.20 (D1)
/USB3-1-D_N: J1.A7 (DN1), J1.B7 (DN2), J3.14, U5.19 (D2)
/USB3-1-D_P: J1.A6 (DP1), J1.B6 (DP2), J3.13, U5.20 (D1)
/USBL_J1_EN: J3.8, R21.2
/USBL_J1_FAULT_N: J3.4, R19.2
/USBL_J1_UFP_N: J3.7, R20.2
/USBL_PD_PG_N: J3.1, R16.2
/USBL_U3_FLT_N: J3.2, R17.2
/USBL_U5_FLT_N: J3.3, R18.2
/VBUS_PD: C15.1, C16.1, C17.1, D7.4 (VDD/IO), D7.5 (VDD/IO), D7.6 (VDD/IO), J5.1, J5.2, J5.3, J5.4, J5.5, Q2.5 (D), Q2.6 (D), Q2.7 (D), Q2.8 (D)

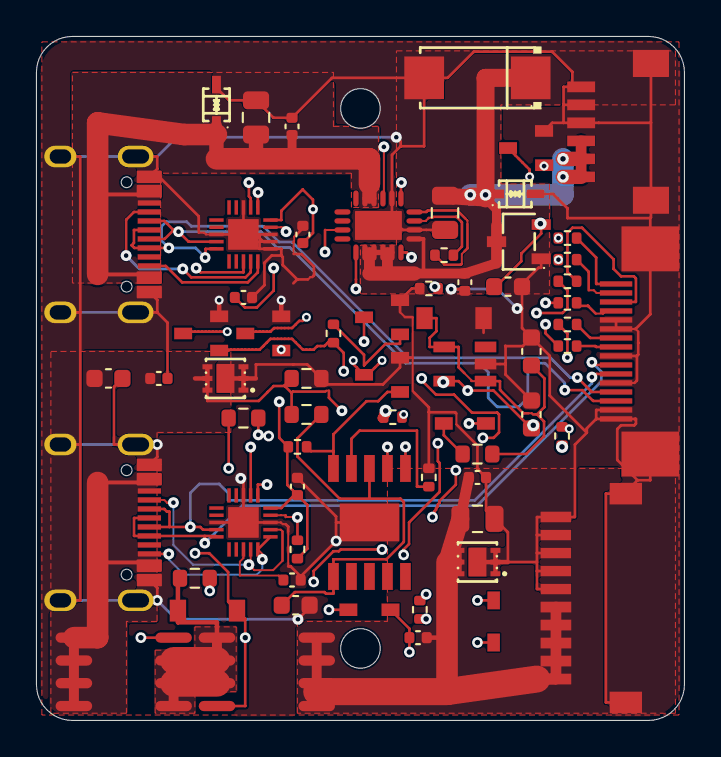
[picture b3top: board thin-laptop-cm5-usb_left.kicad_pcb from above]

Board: 4 copper layers, 36.0 x 38.0 mm, 67 parts (0 on the bottom side), 49 nets.

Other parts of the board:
H1, H2: MountingHole_2.2mm_M2
